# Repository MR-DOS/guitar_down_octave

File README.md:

# guitar_down_octave
----
## Description
This is an analog guitar effect which works as octave-down effect. Contrary to all available analog octave-down effect (let me know if you find one!), it produces undistorted sinewave (when supplied with pure sinewave on input). There is no PLL, no oscillator

----
## Overview
So, you may want to know how it works. A long time ago, I was experimenting with octave-up effects. Recently, I thought that the principle of octave-up effects can be turned inside-out and a bit expanded to make an octave-down effect. The way most octave-up effects work (the good ones, simple ones only rectify the input waveform which is horrible) is as follows:

=\frac{sin(2x)}{2}+\frac{1}{2})

If this function is inverted, you get:

}{2}+\frac{1}{2}}=|sin(\frac{x}{2})|)

However, this is not enough to turn sinewave into sinewave of half frequency. You need to remove the absolute value and this is where the analog mojo kicks in.
If you want more insight, look in the presentation where simulated waveforms can be found. If you are more curious, look into the schematics or simulation.

----
## Explanation of function
To sum it up, the circuit does the following: detect input amplitude and shift the input signal in such a way that the sinewave has its minimum at precisely 0 Vdc, find a square root of the shifted signal and normalize its amplitude so that input and output amplitudes are equal, then invert the signal at points where it gets closest to zero.

### 90deg phasing circuit
In order to detect extremes, you need to detect zero crossing of a derivation of the input signal. Initially, derivator was used, but it had several issues, most importantly its sensitivity was increasing with frequency whereas I needed quite the opposite, because the circuit needs to be most sensitive in the range of tens of Hz to several hundreds of Hz. The sensitivity also should decrease with rising frequency to make the phasing circuit more immune to harmonics (because signal from guitar is going to be flooded with harmonics). So a double integrator was used - one for the phasing circuit, one as DC servo. However, this circuit has a nasty peak at 32 Hz, so it had to be compensated with a Twin-T notch filter right on the input of the whole effect. It maintains proper 90deg +- 0.25deg phase from about 60 Hz and up. There is an additional RC T-network to accelerate convergence to 90deg at low frequencies, which allows for more gain in the integrator by using shorter time constant. It should work even with harmonic-rich signals, however the harmonics must be in phase (and not antiphase) with the fundamental frequency, otherwise an analysis of what will happen is nontrivial.

Schematics of the input circuit with the notch filter and the phasing circuit:

Green sine is the input waveform, blue is the 90deg shifted sine, red is output of the comparator:

### Synchronous peak detector
There is a synchronous peak detector which uses 2 track-and-hold amplifiers (historical LF398). One of them tracks the input signal while the second one holds a peak value. Each time the input waveform goes through one of its extremes, their tasks are switched. At the same time, an analog switch selects the one which holds the peak value. This way, you get a fairly precise DC value representing the amplitude which is updated after each cycle of the sinewave. This was needed because regular peak detectors were too slow to react fast enough to dynamics of playing a guitar while being too fast to hold their value during the whole cycle of sinewave, so they would cause a lot of distortion and bad dynamics.
This part and the phasing circuit proved to be crucial for proper operation of the whole effect.

Green sine is the input waveform, blue and light blue waveforms are outputs of the track-and-hold amplifiers:

### Square root finder
The square root finder is quite simple - it uses opamps and diodes to calculate the logarithm of the DC shifted signal, then divide by two (simple resistor divider) and exponentiate. This computes the square root even with proper sign. The only problem is very low speed of this circuit when crossing zero (which is why it never should cross the zero), because it momentarily goes open-loop and has to cross about 1.3 V rapidly.

Square-root-finder schematics:

Waveforms in the square-root-finder:

### Synchronous inverter
To get rid of the absolute value, there is a synchronous inverter which inverts every second halfperiod of the sinewave. This uses the phasing circuit and 74HC74 to generate half frequency square wave which drives an analog switch which selects either positive or negative halfperiod of the sinewave. There is a simple RC filter to suppress crossover distortion.

Green and light blue line are the noninverted and inverted value, dark blue is the combined waveform:

### AGC
To compensate for amplitude error due to the square-root, there is an AGC which uses Gilbert cells. Each square-root-finder is preceded by the Gilbert cell (there are 2), one has the sine wave as input, the second one gets the DC value of amplitude. The AGC tries to get the input and output amplitude the same.

Gilbert cell used as controlled amplifier:

Feedback used to compute the AGC value:

----
### Performance
Performance at 110 Hz, 1Vpk-pk:
The largest harmonic is the 3rd with -62.3 dBc, the THD is about 0.43% or 2.97% depending on how you define the THD. For a nonlinear guitar effect, it is probably satisfactory.

Image of FFT in simulation:

----
## Images of the board
Top view:

Bottom view:

Top view, drilled and with vias in place:

Bottom view, drilled and with vias in place:

Assembled board:

----
## Known bugs
The -15 V switching power supply is a piece of shit. I will never EVER use MC34063, at least for negative power supply. The modern positive switching power supply is OK, it draws only tens of mA. The MC34063 draws one or two orders of magnitude larger current. Maybe it could be replaced by charge pump taken from the positive switching power supply - this means replacing the whole negative power supply by 2 diodes and 1 capacitor.

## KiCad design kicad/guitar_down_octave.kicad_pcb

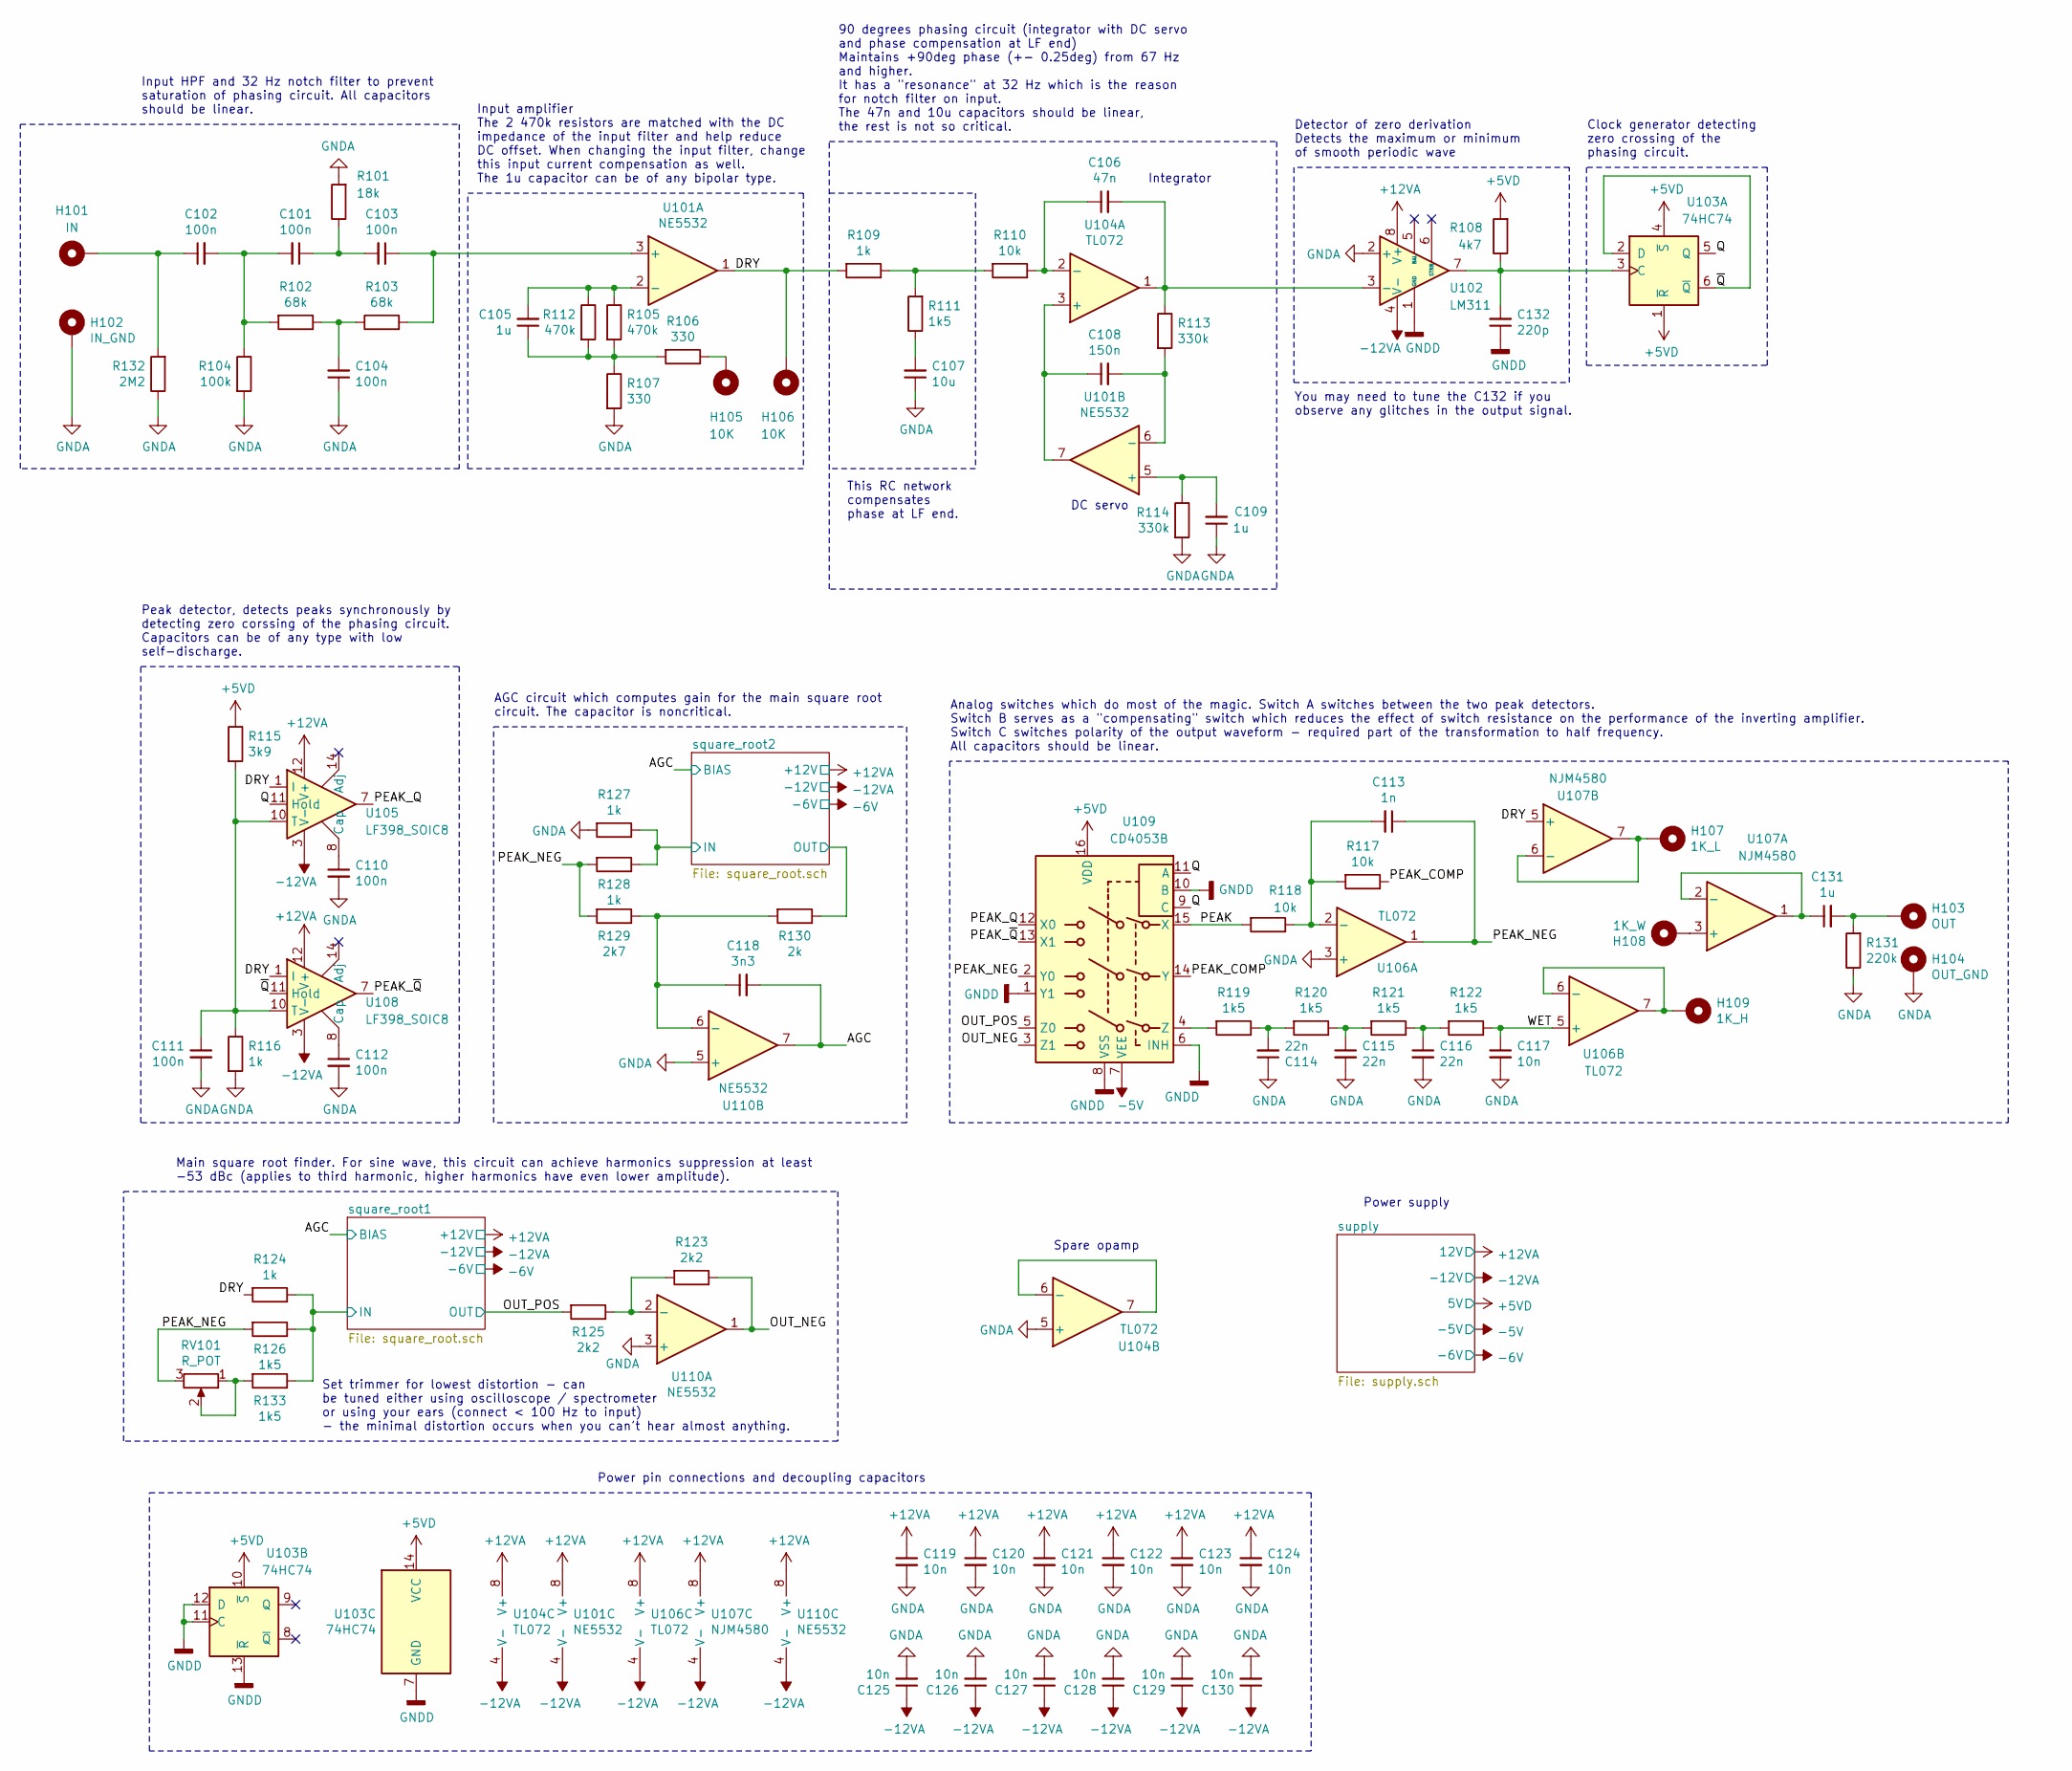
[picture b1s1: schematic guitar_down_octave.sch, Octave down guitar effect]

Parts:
C101, C102, C103, C104: 100n; C_Rect_L7.2mm_W2.5mm_P5.00mm_FKS2_FKP2_MKS2_MKP2
C105, C109: 1u; C_0805_2012Metric_Pad1.15x1.40mm_HandSolder
C106: 47n; C_Rect_L7.2mm_W2.5mm_P5.00mm_FKS2_FKP2_MKS2_MKP2
C107: 10u; C_Rect_L7.2mm_W7.2mm_P5.00mm_FKS2_FKP2_MKS2_MKP2
C108: 150n; C_0805_2012Metric_Pad1.15x1.40mm_HandSolder
C110, C111, C112: 100n; C_0805_2012Metric_Pad1.15x1.40mm_HandSolder
C113: 1n; C_0805_2012Metric_Pad1.15x1.40mm_HandSolder
C114, C115, C116: 22n; C_Rect_L7.2mm_W2.5mm_P5.00mm_FKS2_FKP2_MKS2_MKP2
C117: 10n; C_Rect_L7.2mm_W2.5mm_P5.00mm_FKS2_FKP2_MKS2_MKP2
C118: 3n3; C_0805_2012Metric_Pad1.15x1.40mm_HandSolder
C119, C120, C121, C122, C123, C124, C125, C126, C127, C128, C129, C130: 10n; C_0805_2012Metric_Pad1.15x1.40mm_HandSolder
C131: 1u; C_Rect_L7.2mm_W7.2mm_P5.00mm_FKS2_FKP2_MKS2_MKP2
C132: 220p; C_0805_2012Metric_Pad1.15x1.40mm_HandSolder
H101: IN; MountingHole_2.2mm_M2_Pad
H102: IN_GND; MountingHole_2.2mm_M2_Pad
H103: OUT; MountingHole_2.2mm_M2_Pad
H104: OUT_GND; MountingHole_2.2mm_M2_Pad
H105, H106: 10K; MountingHole_2.2mm_M2_Pad
H107: 1K_L; MountingHole_2.2mm_M2_Pad
H108: 1K_W; MountingHole_2.2mm_M2_Pad
H109: 1K_H; MountingHole_2.2mm_M2_Pad
R101: 18k; R_0805_2012Metric_Pad1.15x1.40mm_HandSolder
R102, R103: 68k; R_0805_2012Metric_Pad1.15x1.40mm_HandSolder
R104: 100k; R_0805_2012Metric_Pad1.15x1.40mm_HandSolder
R105, R112: 470k; R_0805_2012Metric_Pad1.15x1.40mm_HandSolder
R106, R107: 330; R_0805_2012Metric_Pad1.15x1.40mm_HandSolder
R108: 4k7; R_0805_2012Metric_Pad1.15x1.40mm_HandSolder
R109, R116, R124, R127, R128: 1k; R_0805_2012Metric_Pad1.15x1.40mm_HandSolder
R110, R117, R118: 10k; R_0805_2012Metric_Pad1.15x1.40mm_HandSolder
R111, R119, R120, R121, R122, R126, R133: 1k5; R_0805_2012Metric_Pad1.15x1.40mm_HandSolder
R113, R114: 330k; R_0805_2012Metric_Pad1.15x1.40mm_HandSolder
R115: 3k9; R_0805_2012Metric_Pad1.15x1.40mm_HandSolder
R123, R125: 2k2; R_0805_2012Metric_Pad1.15x1.40mm_HandSolder
R129: 2k7; R_0805_2012Metric_Pad1.15x1.40mm_HandSolder
R130: 2k; R_0805_2012Metric_Pad1.15x1.40mm_HandSolder
R131: 220k; R_0805_2012Metric_Pad1.15x1.40mm_HandSolder
R132: 2M2; R_0805_2012Metric_Pad1.15x1.40mm_HandSolder
RV101: R_POT; Potentiometer_Bourns_3296Y_Vertical
U101, U110: NE5532; SOIC-8_3.9x4.9mm_P1.27mm
U102: LM311; SOIC-8_3.9x4.9mm_P1.27mm
U103: 74HC74; SOIC-14_3.9x8.7mm_P1.27mm
U104, U106: TL072; SOIC-8_3.9x4.9mm_P1.27mm
U105, U108: LF398_SOIC8; SOIC-14_3.9x8.7mm_P1.27mm
U107: NJM4580; SOIJ-8_5.3x5.3mm_P1.27mm
U109: CD4053B; SOIC-16_3.9x9.9mm_P1.27mm

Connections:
+5VD: R108.2, R115.1, U103.1 (~R), U103.4 (~S), U103.10 (~S), U103.14 (VCC), U109.16 (VDD); also elsewhere on the board
+12VA: C119.1, C120.1, C121.1, C122.1, C123.1, C124.1, U101.8 (V+), U102.8 (V+), U104.8 (V+), U105.12 (V+), U106.8 (V+), U107.8 (V+), U108.12 (V+), U110.8 (V+); also elsewhere on the board
-5V: U109.7 (VEE); also elsewhere on the board
-12VA: C125.1, C126.1, C127.1, C128.1, C129.1, C130.1, U101.4 (V-), U102.4 (V-), U104.4 (V-), U105.3 (V-), U106.4 (V-), U107.4 (V-), U108.3 (V-), U110.4 (V-); also elsewhere on the board
/AGC: C118.2, U110.7; also elsewhere on the board
/DRY: H106.1, R109.2, R124.2, U101.1, U105.1 (I), U107.5 (+), U108.1 (I)
/OUT_NEG: R123.1, U109.3 (Z1), U110.1
/OUT_POS: R125.2, U109.5 (Z0); also elsewhere on the board
/PEAK: R118.2, U109.15 (X)
/PEAK_COMP: R117.1, U109.14 (Y)
/PEAK_NEG: C113.1, R126.2, R128.2, R129.2, RV101.3, U106.1, U109.2 (Y0)
/PEAK_Q: U105.7, U109.12 (X0)
/PEAK_~Q: U108.7, U109.13 (X1)
/Q: U103.5 (Q), U105.11 (Hold), U109.9 (C), U109.11 (A)
/WET: C117.1, R122.1, U106.5 (+)
/square_root1/IN: R124.1, R126.1, R133.1; also elsewhere on the board
/square_root2/IN: R127.1, R128.1; also elsewhere on the board
/square_root2/OUT: R130.1; also elsewhere on the board
/~Q: U103.2 (D), U103.6 (~Q), U108.11 (Hold)
GNDA: C104.1, C107.1, C109.1, C110.2, C111.2, C112.2, C114.1, C115.2, C116.2, C117.2, C119.2, C120.2, C121.2, C122.2, C123.2, C124.2, C125.2, C126.2, C127.2, C128.2, C129.2, C130.2, C132.1, H102.1, H104.1, R101.2, R104.2, R107.2, R114.2, R116.2, R127.2, R131.1, R132.1, U102.1 (GND), U102.2 (+), U103.7 (GND), U103.11 (C), U103.12 (D), U103.13 (~R), U104.5 (+), U106.3 (+), U109.1 (Y1), U109.6 (INH), U109.8 (VSS), U109.10 (B), U110.3 (+), U110.5 (+); also elsewhere on the board
unnamed: C101.1, C103.2, R101.1
unnamed: C101.2, C102.2, R102.2, R104.1
unnamed: C102.1, H101.1, R132.2
unnamed: C103.1, R103.2, U101.3 (+)
unnamed: C104.2, R102.1, R103.1
unnamed: C105.1, R105.2, R106.2, R107.1, R112.2
unnamed: C105.2, R105.1, R112.1, U101.2 (-)
unnamed: C106.1, R110.1, U104.2 (-)
unnamed: C106.2, R113.1, U102.3 (-), U104.1
unnamed: C107.2, R111.1
unnamed: C108.1, U101.7, U104.3 (+)
unnamed: C108.2, R113.2, U101.6 (-)
unnamed: C109.2, R114.1, U101.5 (+)
unnamed: C110.1, U105.8 (Cap)
unnamed: C111.1, R115.2, R116.1, U105.10 (T), U108.10 (T)
unnamed: C112.1, U108.8 (Cap)
unnamed: C113.2, R117.2, R118.1, U106.2 (-)
unnamed: C114.2, R119.1, R120.2
unnamed: C115.1, R120.1, R121.2
unnamed: C116.1, R121.1, R122.2
unnamed: C118.1, R129.1, R130.2, U110.6 (-)
unnamed: C131.1, U107.1, U107.2 (-)
unnamed: C131.2, H103.1, R131.2
unnamed: C132.2, R108.1, U102.7, U103.3 (C)
unnamed: H105.1, R106.1
unnamed: H107.1, U107.6 (-), U107.7
unnamed: H108.1, U107.3 (+)
unnamed: H109.1, U106.6 (-), U106.7
unnamed: R109.1, R110.2, R111.2
unnamed: R119.2, U109.4 (Z)
unnamed: R123.2, R125.1, U110.2 (-)
unnamed: R133.2, RV101.1, RV101.2
unnamed: U104.6 (-), U104.7

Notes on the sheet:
Input HPF and 32 Hz notch filter to prevent saturation of phasing circuit. All capacitors should be linear.
90 degrees phasing circuit (integrator with DC servo and phase compensation at LF end) Maintains +90deg phase (+- 0.25deg) from 67 Hz and higher. It has a "resonance" at 32 Hz which is the reason for notch filter on input. The 47n and 10u capacitors should be linear, the rest is not so critical.
Detector of zero derivation Detects the maximum or minimum of smooth periodic wave
Input amplifier The 2 470k resistors are matched with the DC impedance of the input filter and help reduce DC offset. When changing the input filter, change this input current compensation as well. The 1u capacitor can be of any bipolar type.
This RC network compensates phase at LF end.
Integrator
DC servo
Peak detector, detects peaks synchronously by detecting zero corssing of the phasing circuit. Capacitors can be of any type with low self-discharge.
Clock generator detecting zero crossing of the phasing circuit.
Analog switches which do most of the magic. Switch A switches between the two peak detectors. Switch B serves as a "compensating" switch which reduces the effect of switch resistance on the performance of the inverting amplifier. Switch C switches polarity of the output waveform - required part of 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
AGC circuit which computes gain for the main square root circuit. The capacitor is noncritical.
Main square root finder. For sine wave, this circuit can achieve harmonics suppression at least -53 dBc (applies to third harmonic, higher harmonics have even lower amplitude).
Spare opamp
Power pin connections and decoupling capacitors
Power supply
Set trimmer for lowest distortion - can be tuned either using oscilloscope / spectrometer or using your ears (connect < 100 Hz to input) - the minimal distortion occurs when you can't hear almost anything.
You may need to tune the C132 if you observe any glitches in the output signal.

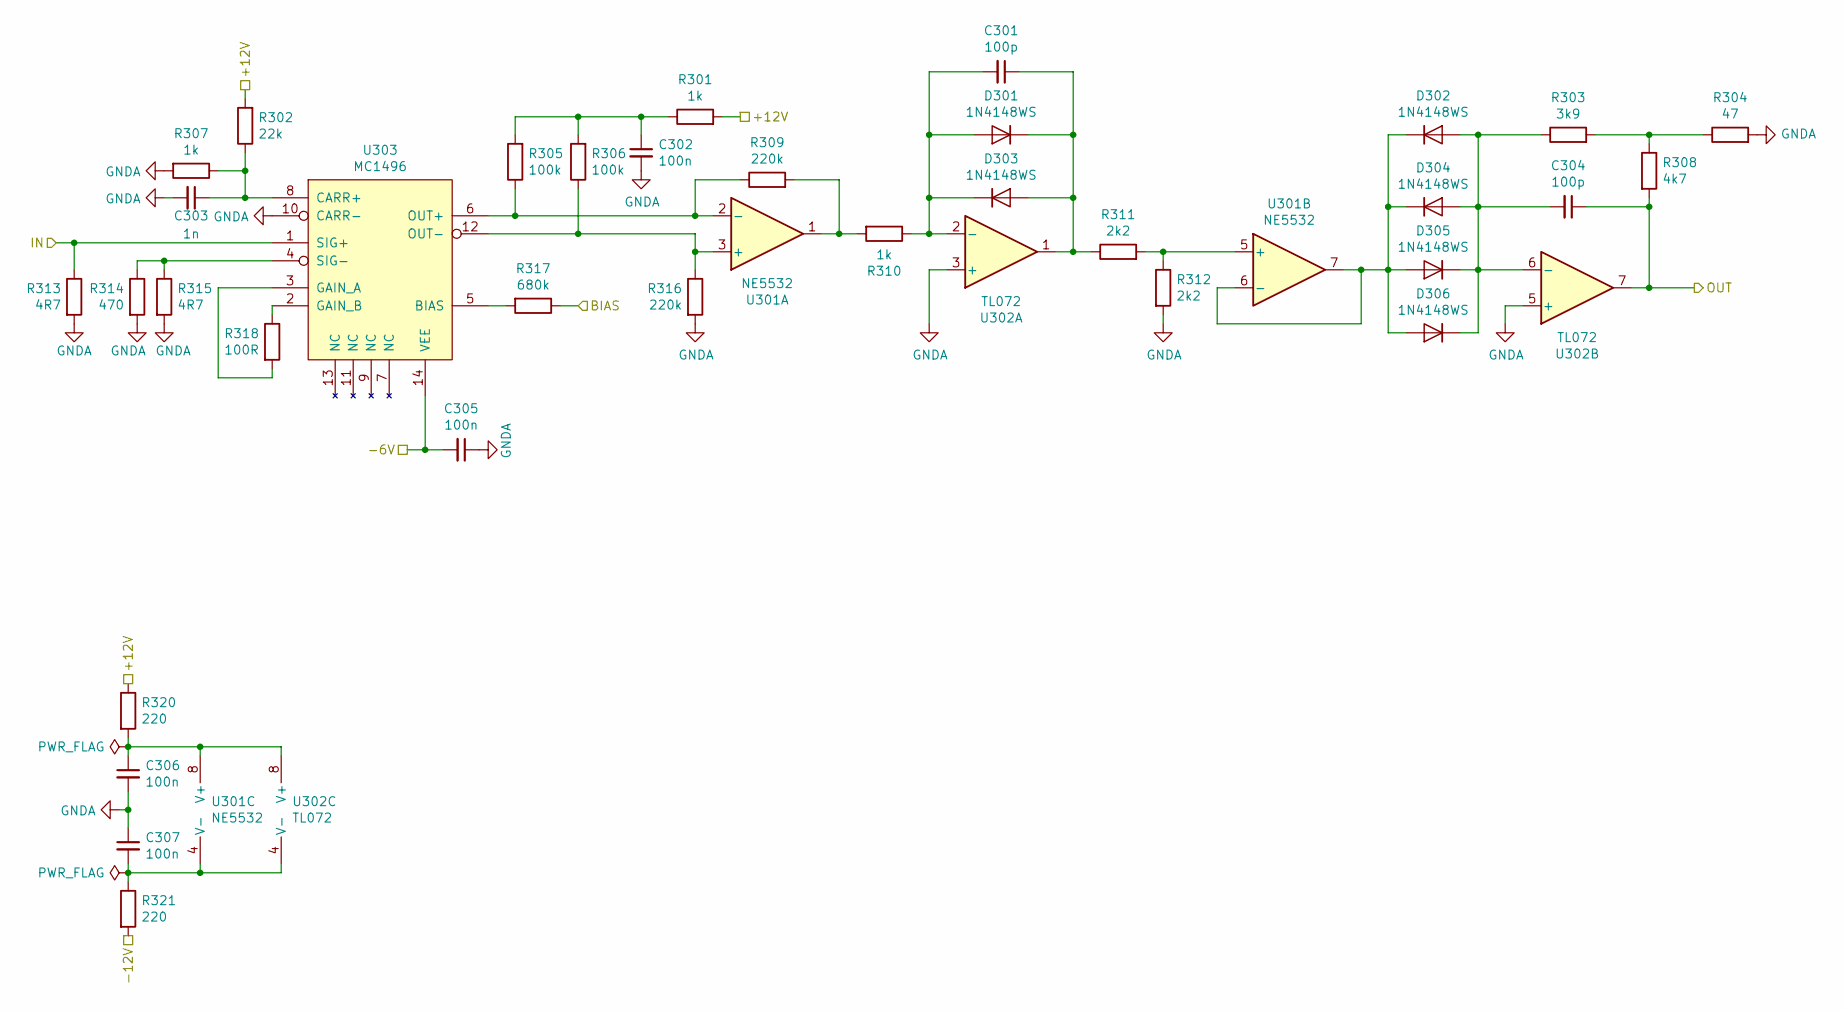
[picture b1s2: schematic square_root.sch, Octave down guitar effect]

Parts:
C201, C204: 100p; C_0805_2012Metric_Pad1.15x1.40mm_HandSolder
C202, C205, C206, C207: 100n; C_0805_2012Metric_Pad1.15x1.40mm_HandSolder
C203: 1n; C_0805_2012Metric_Pad1.15x1.40mm_HandSolder
D201, D202, D203, D204, D205, D206: 1N4148WS; D_SOD-323_HandSoldering
R201, R207, R210: 1k; R_0805_2012Metric_Pad1.15x1.40mm_HandSolder
R202: 22k; R_0805_2012Metric_Pad1.15x1.40mm_HandSolder
R203: 3k9; R_0805_2012Metric_Pad1.15x1.40mm_HandSolder
R204: 47; R_0805_2012Metric_Pad1.15x1.40mm_HandSolder
R205, R206: 100k; R_0805_2012Metric_Pad1.15x1.40mm_HandSolder
R208: 4k7; R_0805_2012Metric_Pad1.15x1.40mm_HandSolder
R209, R216: 220k; R_0805_2012Metric_Pad1.15x1.40mm_HandSolder
R211, R212: 2k2; R_0805_2012Metric_Pad1.15x1.40mm_HandSolder
R213, R215: 4R7; R_0805_2012Metric_Pad1.15x1.40mm_HandSolder
R214: 470; R_0805_2012Metric_Pad1.15x1.40mm_HandSolder
R217: 680k; R_0805_2012Metric_Pad1.15x1.40mm_HandSolder
R218: 100R; R_0805_2012Metric_Pad1.15x1.40mm_HandSolder
R220, R221: 220; R_0805_2012Metric_Pad1.15x1.40mm_HandSolder
U201: NE5532; SOIC-8_3.9x4.9mm_P1.27mm
U202: TL072; SOIC-8_3.9x4.9mm_P1.27mm
U203: MC1496; SOIC-14_3.9x8.7mm_P1.27mm

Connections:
+12VA: R201.2, R202.2, R220.1; also elsewhere on the board
-6V: C205.2, U203.14 (VEE); also elsewhere on the board
-12VA: R221.2; also elsewhere on the board
/AGC: R217.1; also elsewhere on the board
/OUT_POS: C204.1, R208.2, U202.7; also elsewhere on the board
/square_root1/IN: R213.1, U203.1 (SIG+); also elsewhere on the board
GNDA: C202.2, C203.2, C205.1, C206.2, C207.1, R204.2, R207.2, R212.2, R213.2, R214.2, R215.2, R216.2, U202.3 (+), U202.5 (+), U203.10 (CARR-); also elsewhere on the board
unnamed: C201.1, D201.1 (K), D203.2 (A), R211.1, U202.1
unnamed: C201.2, D201.2 (A), D203.1 (K), R210.1, U202.2 (-)
unnamed: C202.1, R201.1, R205.2, R206.2
unnamed: C203.1, R202.1, R207.1, U203.8 (CARR+)
unnamed: C204.2, D202.2 (A), D204.2 (A), D205.1 (K), D206.1 (K), R203.1, U202.6 (-)
unnamed: C206.1, R220.2, U201.8 (V+), U202.8 (V+)
unnamed: C207.2, R221.1, U201.4 (V-), U202.4 (V-)
unnamed: D202.1 (K), D204.1 (K), D205.2 (A), D206.2 (A), U201.6 (-), U201.7
unnamed: R203.2, R204.1, R208.1
unnamed: R205.1, R209.1, U201.2 (-), U203.6 (OUT+)
unnamed: R206.1, R216.1, U201.3 (+), U203.12 (OUT-)
unnamed: R209.2, R210.2, U201.1
unnamed: R211.2, R212.1, U201.5 (+)
unnamed: R214.1, R215.1, U203.4 (SIG-)
unnamed: R217.2, U203.5 (BIAS)
unnamed: R218.1, U203.2 (GAIN_B)
unnamed: R218.2, U203.3 (GAIN_A)

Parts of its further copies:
C301, C304: 100p; C_0805_2012Metric_Pad1.15x1.40mm_HandSolder
C302, C305, C306, C307: 100n; C_0805_2012Metric_Pad1.15x1.40mm_HandSolder
C303: 1n; C_0805_2012Metric_Pad1.15x1.40mm_HandSolder
D301, D302, D303, D304, D305, D306: 1N4148WS; D_SOD-323_HandSoldering
R301, R307, R310: 1k; R_0805_2012Metric_Pad1.15x1.40mm_HandSolder
R302: 22k; R_0805_2012Metric_Pad1.15x1.40mm_HandSolder
R303: 3k9; R_0805_2012Metric_Pad1.15x1.40mm_HandSolder
R304: 47; R_0805_2012Metric_Pad1.15x1.40mm_HandSolder
R305, R306: 100k; R_0805_2012Metric_Pad1.15x1.40mm_HandSolder
R308: 4k7; R_0805_2012Metric_Pad1.15x1.40mm_HandSolder
R309, R316: 220k; R_0805_2012Metric_Pad1.15x1.40mm_HandSolder
R311, R312: 2k2; R_0805_2012Metric_Pad1.15x1.40mm_HandSolder
R313, R315: 4R7; R_0805_2012Metric_Pad1.15x1.40mm_HandSolder
R314: 470; R_0805_2012Metric_Pad1.15x1.40mm_HandSolder
R317: 680k; R_0805_2012Metric_Pad1.15x1.40mm_HandSolder
R318: 100R; R_0805_2012Metric_Pad1.15x1.40mm_HandSolder
R320, R321: 220; R_0805_2012Metric_Pad1.15x1.40mm_HandSolder
U301: NE5532; SOIC-8_3.9x4.9mm_P1.27mm
U302: TL072; SOIC-8_3.9x4.9mm_P1.27mm
U303: MC1496; SOIC-14_3.9x8.7mm_P1.27mm

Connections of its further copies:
+12VA: R301.2, R302.2, R320.1; also elsewhere on the board
-6V: C305.2, U303.14 (VEE); also elsewhere on the board
-12VA: R321.2; also elsewhere on the board
/AGC: R317.1; also elsewhere on the board
/square_root2/IN: R313.1, U303.1 (SIG+); also elsewhere on the board
/square_root2/OUT: C304.1, R308.2, U302.7; also elsewhere on the board
GNDA: C302.2, C303.2, C305.1, C306.2, C307.1, R304.2, R307.2, R312.2, R313.2, R314.2, R315.2, R316.2, U302.3 (+), U302.5 (+), U303.10 (CARR-); also elsewhere on the board
unnamed: C301.1, D301.1 (K), D303.2 (A), R311.1, U302.1
unnamed: C301.2, D301.2 (A), D303.1 (K), R310.1, U302.2 (-)
unnamed: C302.1, R301.1, R305.2, R306.2
unnamed: C303.1, R302.1, R307.1, U303.8 (CARR+)
unnamed: C304.2, D302.2 (A), D304.2 (A), D305.1 (K), D306.1 (K), R303.1, U302.6 (-)
unnamed: C306.1, R320.2, U301.8 (V+), U302.8 (V+)
unnamed: C307.2, R321.1, U301.4 (V-), U302.4 (V-)
unnamed: D302.1 (K), D304.1 (K), D305.2 (A), D306.2 (A), U301.6 (-), U301.7
unnamed: R303.2, R304.1, R308.1
unnamed: R305.1, R309.1, U301.2 (-), U303.6 (OUT+)
unnamed: R306.1, R316.1, U301.3 (+), U303.12 (OUT-)
unnamed: R309.2, R310.2, U301.1
unnamed: R311.2, R312.1, U301.5 (+)
unnamed: R314.1, R315.1, U303.4 (SIG-)
unnamed: R317.2, U303.5 (BIAS)
unnamed: R318.1, U303.2 (GAIN_B)
unnamed: R318.2, U303.3 (GAIN_A)

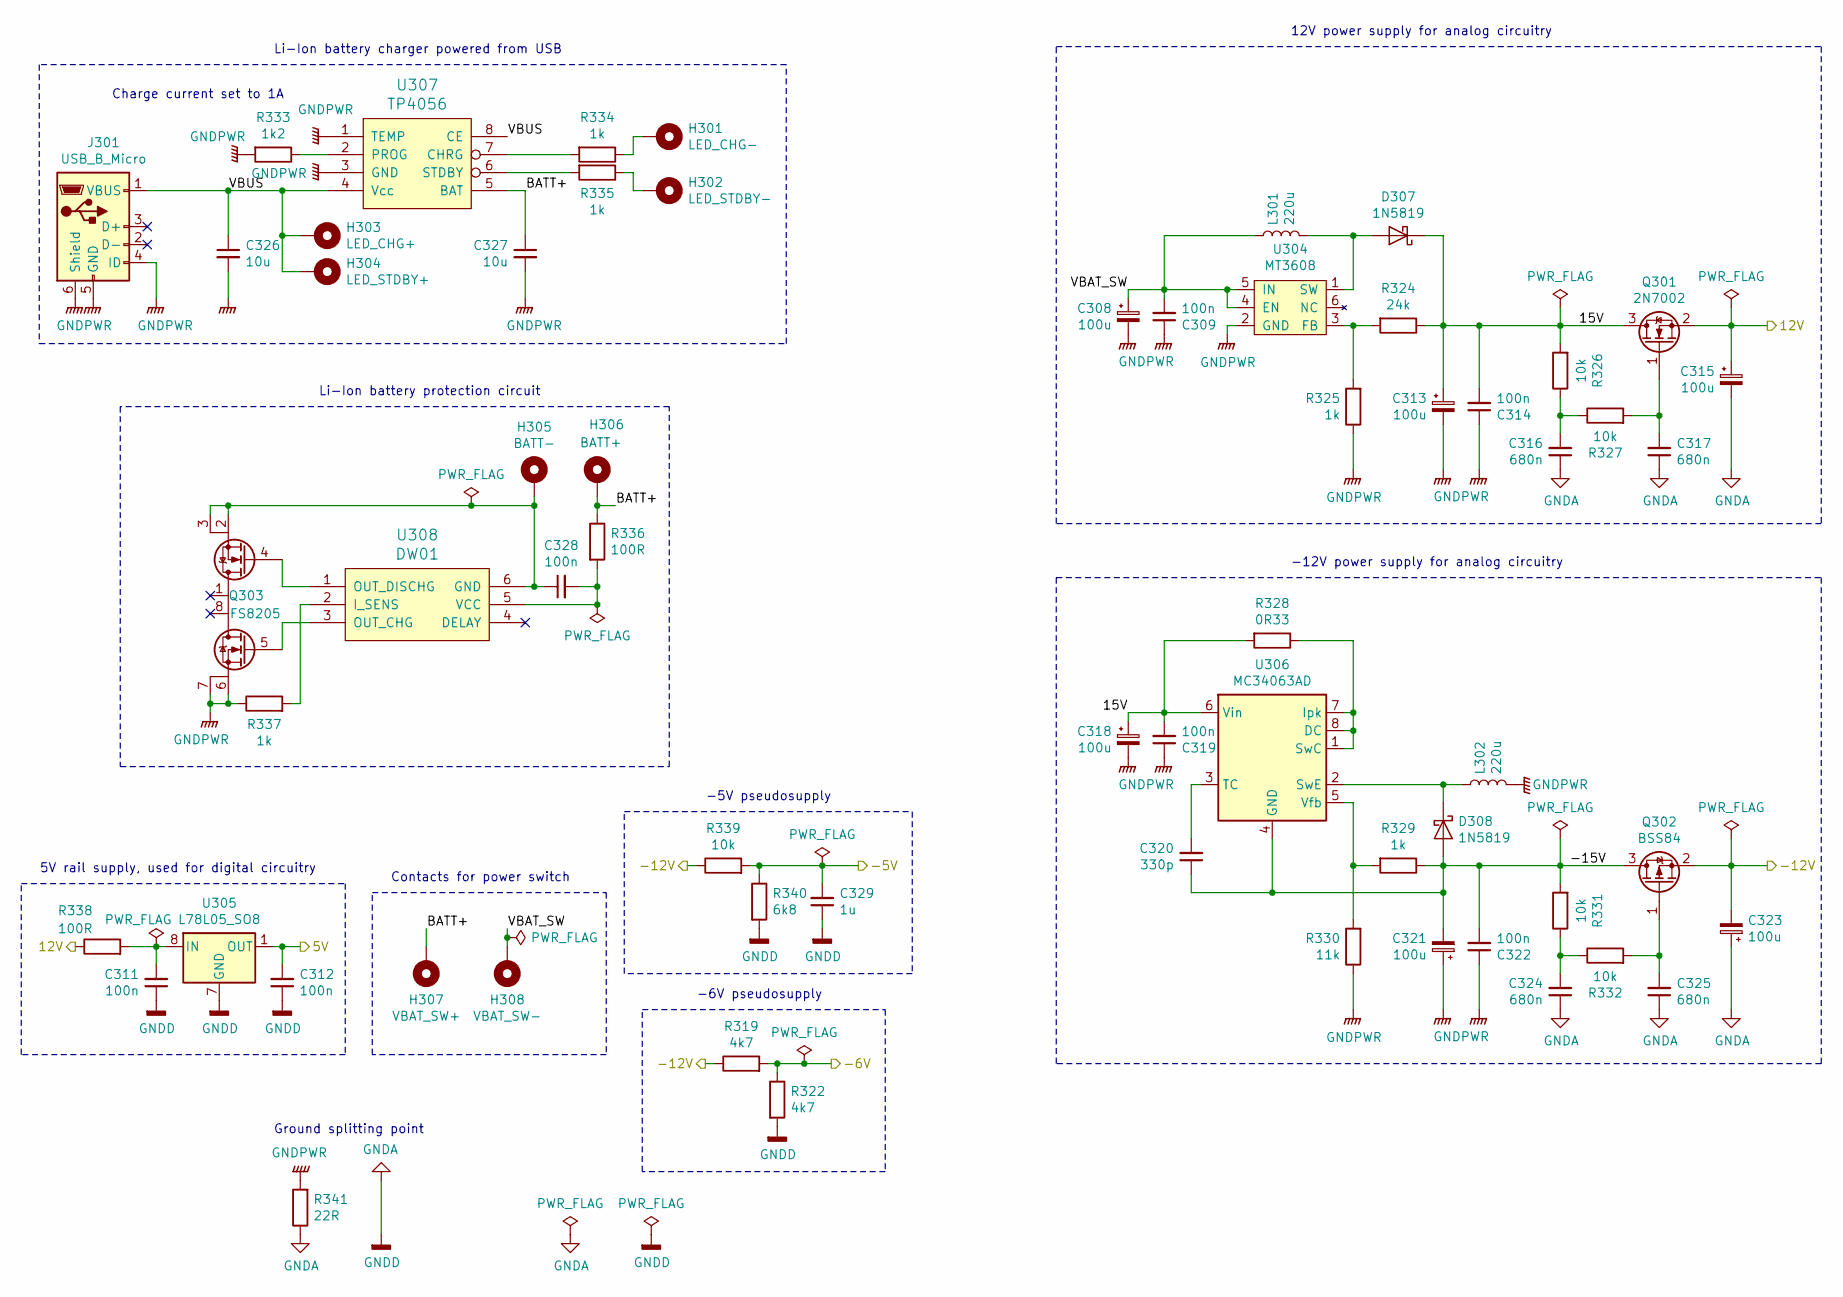
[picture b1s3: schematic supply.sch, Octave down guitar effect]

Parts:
C308, C313, C315, C318, C321, C323: 100u; CP_Elec_8x10
C309, C311, C312, C314, C319, C322, C328: 100n; C_0805_2012Metric_Pad1.15x1.40mm_HandSolder
C316, C317, C324, C325: 680n; C_0805_2012Metric_Pad1.15x1.40mm_HandSolder
C320: 330p; C_0805_2012Metric_Pad1.15x1.40mm_HandSolder
C326, C327: 10u; C_0805_2012Metric_Pad1.15x1.40mm_HandSolder
C329: 1u; C_0805_2012Metric_Pad1.15x1.40mm_HandSolder
D307, D308: 1N5819; D_SOD-123
H301: LED_CHG-; MountingHole_2.2mm_M2_Pad
H302: LED_STDBY-; MountingHole_2.2mm_M2_Pad
H303: LED_CHG+; MountingHole_2.2mm_M2_Pad
H304: LED_STDBY+; MountingHole_2.2mm_M2_Pad
H305: BATT-; MountingHole_2.2mm_M2_Pad
H306: BATT+; MountingHole_2.2mm_M2_Pad
H307: VBAT_SW+; MountingHole_2.2mm_M2_Pad
H308: VBAT_SW-; MountingHole_2.2mm_M2_Pad
J301: USB_B_Micro; USB_Micro-B_Wuerth_629105150521
L301, L302: 220u; L_Wuerth_WE-PD2-Typ-XL
Q301: 2N7002; SOT-23_Handsoldering
Q302: BSS84; SOT-23_Handsoldering
Q303: FS8205; TSSOP-8_4.4x3mm_P0.65mm
R319, R322: 4k7; R_0805_2012Metric_Pad1.15x1.40mm_HandSolder
R324: 24k; R_0805_2012Metric_Pad1.15x1.40mm_HandSolder
R325, R329, R334, R335, R337: 1k; R_0805_2012Metric_Pad1.15x1.40mm_HandSolder
R326, R327, R331, R332, R339: 10k; R_0805_2012Metric_Pad1.15x1.40mm_HandSolder
R328: 0R33; R_1206_3216Metric_Pad1.42x1.75mm_HandSolder
R330: 11k; R_0805_2012Metric_Pad1.15x1.40mm_HandSolder
R333: 1k2; R_0805_2012Metric_Pad1.15x1.40mm_HandSolder
R336, R338: 100R; R_0805_2012Metric_Pad1.15x1.40mm_HandSolder
R340: 6k8; R_0805_2012Metric_Pad1.15x1.40mm_HandSolder
R341: 22R; R_0805_2012Metric_Pad1.15x1.40mm_HandSolder
U304: MT3608; TSOT-23-6_HandSoldering
U305: L78L05_SO8; SOIC-8_3.9x4.9mm_P1.27mm
U306: MC34063AD; SOIC-8_3.9x4.9mm_P1.27mm
U307: TP4056; SOIC-8_3.9x4.9mm_P1.27mm
U308: DW01; SOT-23-6

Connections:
+5VD: C312.2, U305.1 (OUT); also elsewhere on the board
+12VA: C315.1, Q301.2 (S), R338.1; also elsewhere on the board
-5V: C329.2, R339.2, R340.1; also elsewhere on the board
-6V: R319.2, R322.1; also elsewhere on the board
-12VA: C323.2, Q302.2 (S), R319.1, R339.1; also elsewhere on the board
/supply/15V: C313.1, C314.2, C318.1, C319.2, D307.1 (K), Q301.3 (D), R324.1, R326.2, R328.2, U306.6 (Vin)
/supply/-15V: C320.1, C321.2, C322.2, D308.2 (A), Q302.3 (D), R329.1, R331.2, U306.4 (GND)
/supply/BATT+: C327.1, H306.1, H307.1, R336.1, U307.5 (BAT)
/supply/VBAT_SW: C308.1, C309.2, H308.1, L301.1, U304.4 (EN), U304.5 (IN)
/supply/VBUS: C326.1, H303.1, H304.1, J301.1 (VBUS), U307.4 (Vcc), U307.8 (CE)
GNDA: C311.1, C312.1, C315.2, C316.1, C317.1, C323.1, C324.1, C325.1, C329.1, R322.2, R340.2, R341.1, U305.2 (GND), U305.3 (GND), U305.6 (GND), U305.7 (GND); also elsewhere on the board
GNDPWR: C308.2, C309.1, C313.2, C314.1, C318.2, C319.1, C321.1, C322.1, C326.2, C327.2, J301.4 (ID), J301.5 (GND), J301.6 (Shield), L302.2, Q303.6 (S2), Q303.7 (S2), R325.1, R330.1, R333.2, R337.1, R341.2, U304.2 (GND), U307.1 (TEMP), U307.3 (GND)
unnamed: C311.2, R338.2, U305.8 (IN)
unnamed: C316.2, R326.1, R327.1
unnamed: C317.2, Q301.1 (G), R327.2
unnamed: C320.2, U306.3 (TC)
unnamed: C324.2, R331.1, R332.1
unnamed: C325.2, Q302.1 (G), R332.2
unnamed: C328.1, H305.1, Q303.2 (S1), Q303.3 (S1), U308.6 (GND)
unnamed: C328.2, R336.2, U308.5 (VCC)
unnamed: D307.2 (A), L301.2, U304.1 (SW)
unnamed: D308.1 (K), L302.1, U306.2 (SwE)
unnamed: H301.1, R334.1
unnamed: H302.1, R335.1
unnamed: Q303.4 (G1), U308.1 (OUT_DISCHG)
unnamed: Q303.5 (G2), U308.3 (OUT_CHG)
unnamed: R324.2, R325.2, U304.3 (FB)
unnamed: R328.1, U306.1 (SwC), U306.7 (Ipk), U306.8 (DC)
unnamed: R329.2, R330.2, U306.5 (Vfb)
unnamed: R333.1, U307.2 (PROG)
unnamed: R334.2, U307.7 (CHRG)
unnamed: R335.2, U307.6 (STDBY)
unnamed: R337.2, U308.2 (I_SENS)

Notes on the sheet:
Charge current set to 1A
Li-Ion battery charger powered from USB
Li-Ion battery protection circuit
5V rail supply, used for digital circuitry
-12V power supply for analog circuitry
12V power supply for analog circuitry
Contacts for power switch
-5V pseudosupply
Ground splitting point
-6V pseudosupply

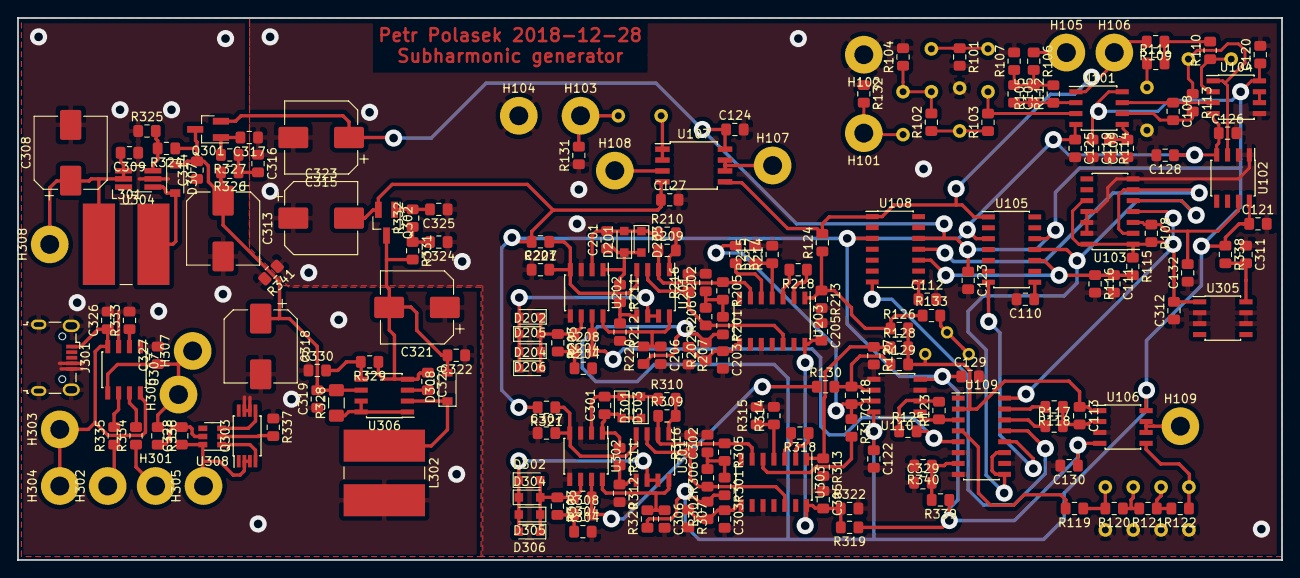
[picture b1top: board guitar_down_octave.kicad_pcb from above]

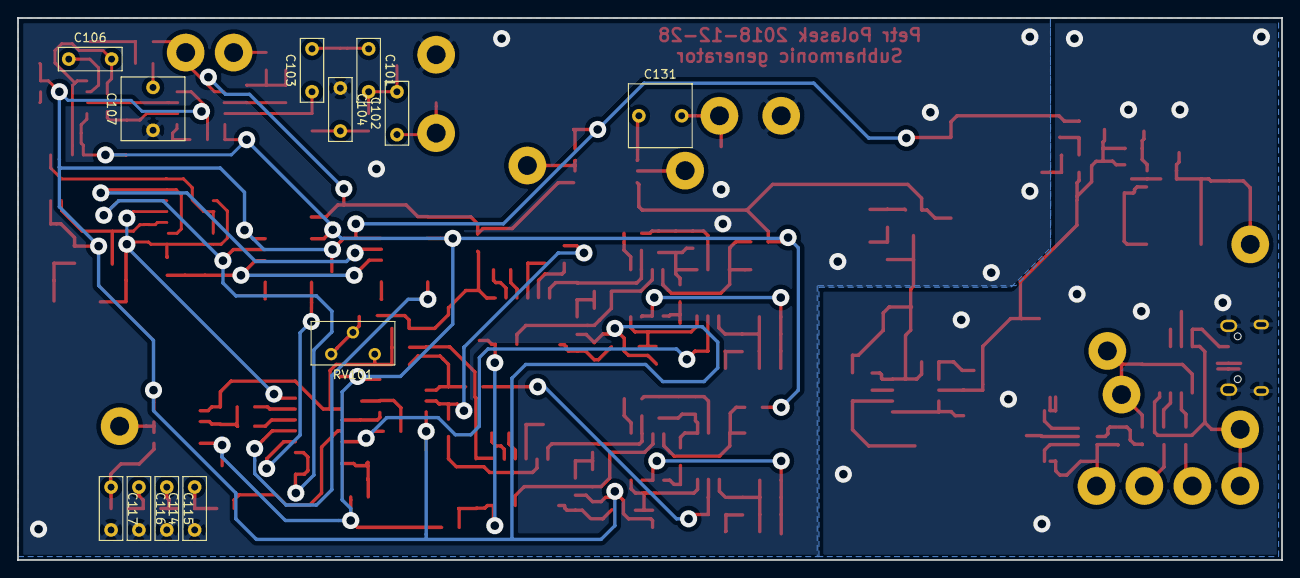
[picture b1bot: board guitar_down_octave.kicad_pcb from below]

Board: 2 copper layers, 147.4 x 63.2 mm, 219 parts (12 on the bottom side), 115 nets.

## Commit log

2019-01-13 First version
2019-01-14 Corrections to the README due to wrong image links
2019-01-14 Corrections to the README due to formatting of equations
2019-01-14 Fixed a typo in the second equation
2019-01-14 Fixed another typo in the second equation
2021-11-23 Create LICENSE
    Added GPLv3 license
